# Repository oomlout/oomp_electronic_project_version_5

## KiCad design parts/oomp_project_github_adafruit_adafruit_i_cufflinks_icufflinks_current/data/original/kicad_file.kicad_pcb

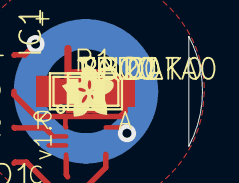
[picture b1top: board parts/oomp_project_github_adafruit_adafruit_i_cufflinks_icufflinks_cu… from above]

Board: 2 copper layers, 12 parts (0 on the bottom side), 7 nets.

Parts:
GND0: TPTP10R; TP10R
IC1: ATTINY10-MAHR; UDFN-8
LED1: SMLK34
PB2: TPTP10R; TP10R
R1: R0805
RST0: TPTP10R; TP10R
TPICLK0: TPTP10R; TP10R
TPIDATA0: TPTP10R; TP10R
U$1: ADAFRUIT200MIL
U$2, U$3: FIDUCIAL; TP_SIGNAL_NAME!
VCC0: TPTP10R; TP10R

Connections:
B0: IC1.5, LED1.K, TPIDATA0.TP
B1: IC1.1, TPICLK0.TP
B2: IC1.8, PB2.TP
GND: GND0.TP, IC1.4
unnamed: LED1.A, R1.1
RST: IC1.6, RST0.TP
VCC: IC1.7, R1.2, VCC0.TP

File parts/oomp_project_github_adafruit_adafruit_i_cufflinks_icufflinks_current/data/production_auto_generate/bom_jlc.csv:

Comment,Designator,Footprint,LCSC Part #
,U$1,cuff-import-fps:ADAFRUIT200MIL,
,R1,cuff-import-fps:R0805,
,LED1,cuff-import-fps:SMLK34,
ATTINY10-MAHR,IC1,cuff-import-fps:UDFN-8,
FIDUCIAL,"U$2,U$3",cuff-import-fps:TP_SIGNAL_NAME!,
TPTP10R,"GND0,PB2,RST0,TPICLK0,TPIDATA0,VCC0",cuff-import-fps:TP10R,

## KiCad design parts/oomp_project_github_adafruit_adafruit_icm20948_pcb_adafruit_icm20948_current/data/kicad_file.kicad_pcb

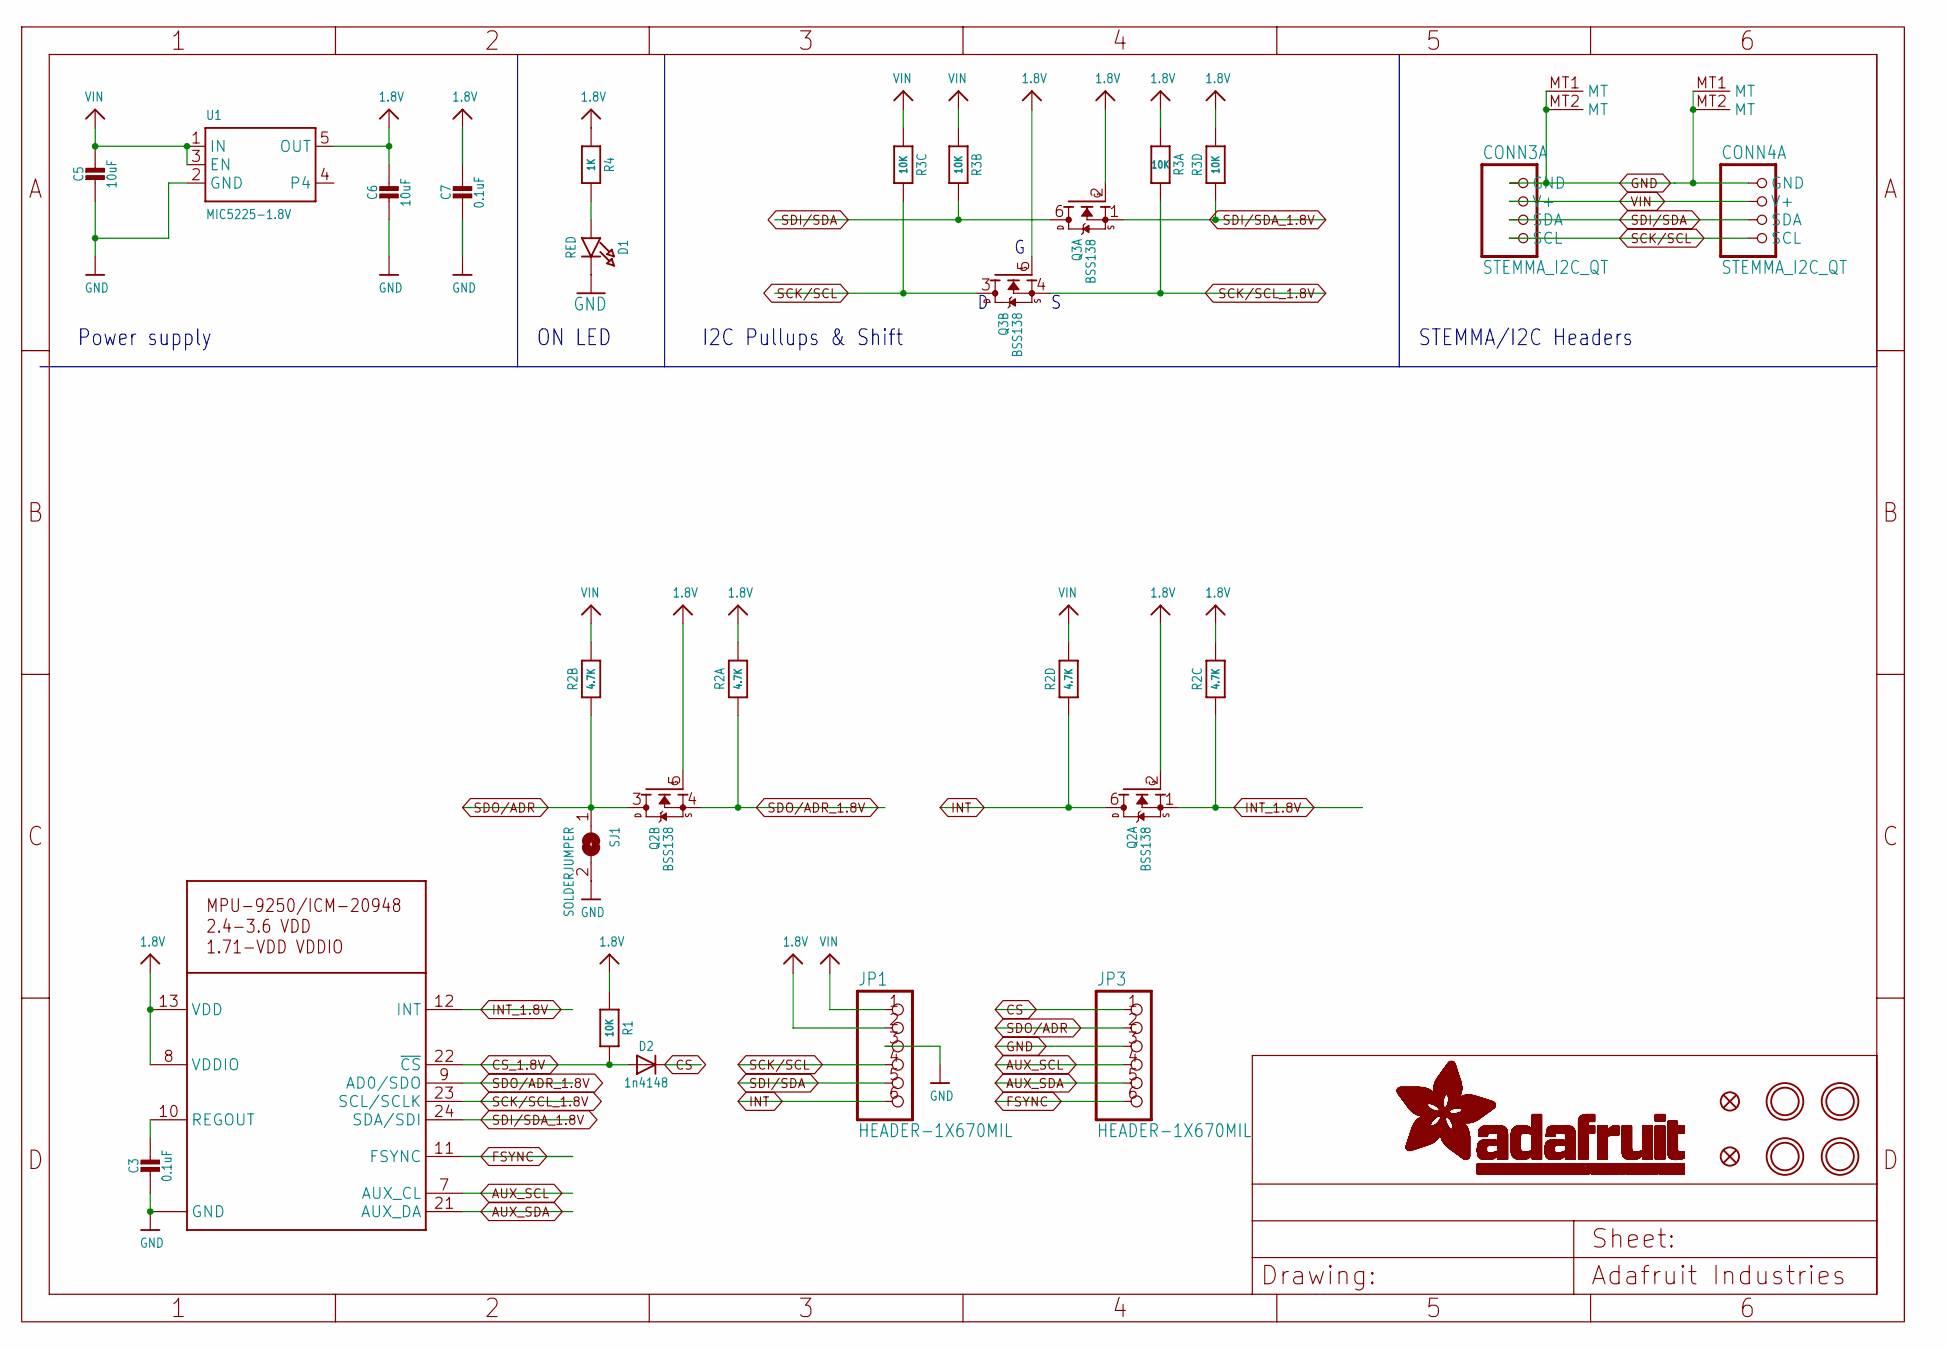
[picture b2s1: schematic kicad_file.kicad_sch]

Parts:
C3, C7: 0.1uF; 0603-NO
C5, C6: 10uF; 0805-NO
CONN3, CONN4: STEMMA_I2C_QT; JST_SH4
D1: RED; CHIPLED_0603_NOOUTLINE
D2: 1n4148; SOD-323_MINI
FID2, FID4: FIDUCIAL_1MM
JP1, JP3: HEADER-1X670MIL; 1X06_ROUND_70
Q2, Q3: BSS138; SOT363
R1: 10K; 0603-NO
R2: 4.7K; RESPACK_4X0603
R3: 10K; RESPACK_4X0603
R4: 1K; 0603-NO
SJ1: SOLDERJUMPER; SOLDERJUMPER_ARROW_NOPASTE
U1: MIC5225-1.8V; SOT23-5
U$21: MPU-9250_ICM20948; QFN24_3MM_NOEP
U$38, U$39, U$41, U$42: MOUNTINGHOLE2.5; MOUNTINGHOLE_2.5_PLATED

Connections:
1.8V: C6.1, C7.1, JP1.2, Q2.2 (G), Q2.5 (G), Q3.2 (G), Q3.5 (G), R1.1, R2.6 (2), R2.8 (2), R3.4 (1), R3.8 (2), R4.1, U1.5 (OUT), U$21.8 (VDDIO), U$21.13 (VDD)
AUX_SCL: JP3.4, U$21.7 (AUX_CL)
AUX_SDA: JP3.5, U$21.21 (AUX_DA)
CS: D2.C, JP3.1
CS_1.8V: D2.A, R1.2, U$21.22 (~CS)
FSYNC: JP3.6, U$21.11 (FSYNC)
GND: C3.2, C5.2, C6.2, C7.2, CONN3.1 (GND), CONN3.MT1 (MT), CONN3.MT2 (MT), CONN4.1 (GND), CONN4.MT1 (MT), CONN4.MT2 (MT), D1.C, JP1.3, JP3.3, SJ1.2, U1.2 (GND), U$21.18 (GND), U$21.20 (GND)
INT: JP1.6, Q2.6 (D), R2.4 (1)
INT_1.8V: Q2.1 (S), R2.3 (1), U$21.12 (INT)
unnamed: D1.A, R4.2
REGOUT: C3.1, U$21.10 (REGOUT)
SCK/SCL: CONN3.4 (SCL), CONN4.4 (SCL), JP1.4, Q3.3 (D), R3.6 (2)
SCK/SCL_1.8V: Q3.4 (S), R3.1, U$21.23 (SCL/SCLK)
SDI/SDA: CONN3.3 (SDA), CONN4.3 (SDA), JP1.5, Q3.6 (D), R3.7 (2)
SDI/SDA_1.8V: Q3.1 (S), R3.5 (2), U$21.24 (SDA/SDI)
SDO/ADR: JP3.2, Q2.3 (D), R2.2 (1), SJ1.1
SDO/ADR_1.8V: Q2.4 (S), R2.1, U$21.9 (AD0/SDO)
VIN: C5.1, CONN3.2 (V+), CONN4.2 (V+), JP1.1, R2.5 (2), R2.7 (2), R3.2 (1), R3.3 (1), U1.1 (IN), U1.3 (EN)

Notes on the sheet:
STEMMA/I2C Headers
Power supply
I2C Pullups & Shift
ON LED

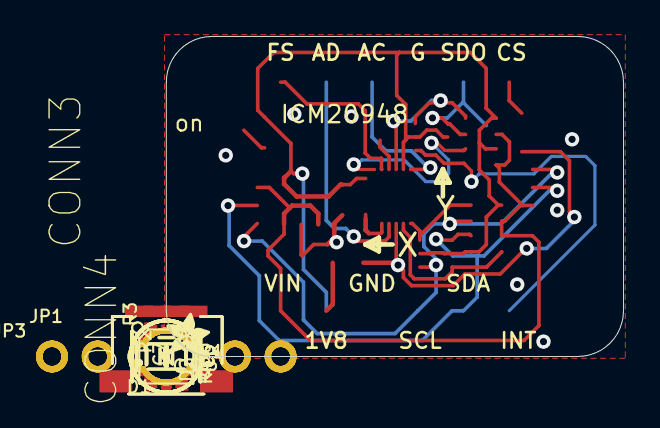
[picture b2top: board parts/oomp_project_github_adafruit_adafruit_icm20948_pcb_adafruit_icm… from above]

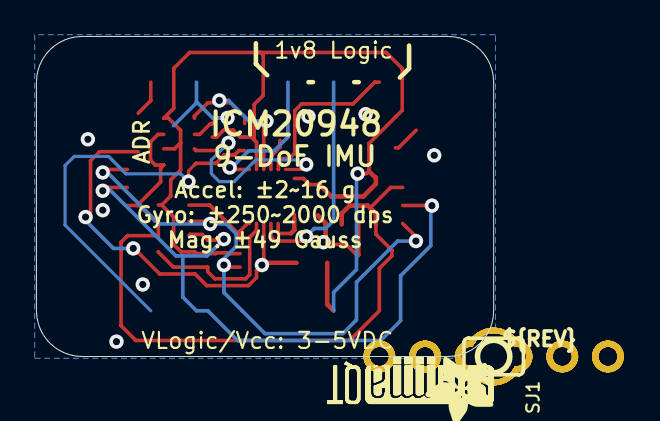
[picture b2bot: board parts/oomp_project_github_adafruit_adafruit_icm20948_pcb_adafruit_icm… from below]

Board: 2 copper layers, 25.4 x 17.8 mm, 30 parts (5 on the bottom side), 18 nets.

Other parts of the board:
U$2: ADAFRUIT_2.5MM
U$12: ADAFRUIT_3.5MM
U$45: PCBFEAT-REV-040
U$46, U$47: STEMMAQT

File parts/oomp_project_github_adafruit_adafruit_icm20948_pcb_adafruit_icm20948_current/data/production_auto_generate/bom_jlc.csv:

Comment,Designator,Footprint,LCSC Part #
,"JP1,JP3",Adafruit ICM20948-import-fps:1X06_ROUND_70,C37208
,U$2,Adafruit ICM20948-import-fps:ADAFRUIT_2.5MM,
,U$12,Adafruit ICM20948-import-fps:ADAFRUIT_3.5MM,
,U$45,Adafruit ICM20948-import-fps:PCBFEAT-REV-040,
,"U$46,U$47",Adafruit ICM20948-import-fps:STEMMAQT,
0.1uF,"C3,C7",Adafruit ICM20948-import-fps:0603-NO,C14663
10K,R1,Adafruit ICM20948-import-fps:0603-NO,C98220
10K,R3,Adafruit ICM20948-import-fps:RESPACK_4X0603,C98220
10uF,"C5,C6",Adafruit ICM20948-import-fps:0805-NO,
1K,R4,Adafruit ICM20948-import-fps:0603-NO,C2907002
1n4148,D2,Adafruit ICM20948-import-fps:SOD-323_MINI,
4.7K,R2,Adafruit ICM20948-import-fps:RESPACK_4X0603,C23162
BSS138,"Q2,Q3",Adafruit ICM20948-import-fps:SOT363,
MIC5225-1.8V,U1,Adafruit ICM20948-import-fps:SOT23-5,
MPU-9250_ICM20948,U$21,Adafruit ICM20948-import-fps:QFN24_3MM_NOEP,
RED,D1,Adafruit ICM20948-import-fps:CHIPLED_0603_NOOUTLINE,
STEMMA_I2C_QT,"CONN3,CONN4",Adafruit ICM20948-import-fps:JST_SH4,C160404

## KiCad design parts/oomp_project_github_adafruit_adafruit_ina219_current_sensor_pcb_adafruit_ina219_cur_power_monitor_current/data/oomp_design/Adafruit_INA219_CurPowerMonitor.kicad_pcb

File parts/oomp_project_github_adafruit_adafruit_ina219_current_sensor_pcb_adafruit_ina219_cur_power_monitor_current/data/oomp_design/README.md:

# OOMP KiCad design copy

Open `Adafruit_INA219_CurPowerMonitor.kicad_pro` (or the `.kicad_pcb` / `.kicad_sch`) in KiCad. Local OOMP libraries are under `libraries/`. Original inputs are preserved in [../original/](../original/).

Only verified unchanged installed KiCad defaults were renamed. Modified, custom, unmatched and unavailable items remain unchanged. Soldering variants are never swapped during conversion. Existing pad coordinates, nets and UUIDs are preserved.

See [conversion_report.yaml](conversion_report.yaml) for every conversion and skip. Copy this directory before editing; regeneration refuses to overwrite edited design files.

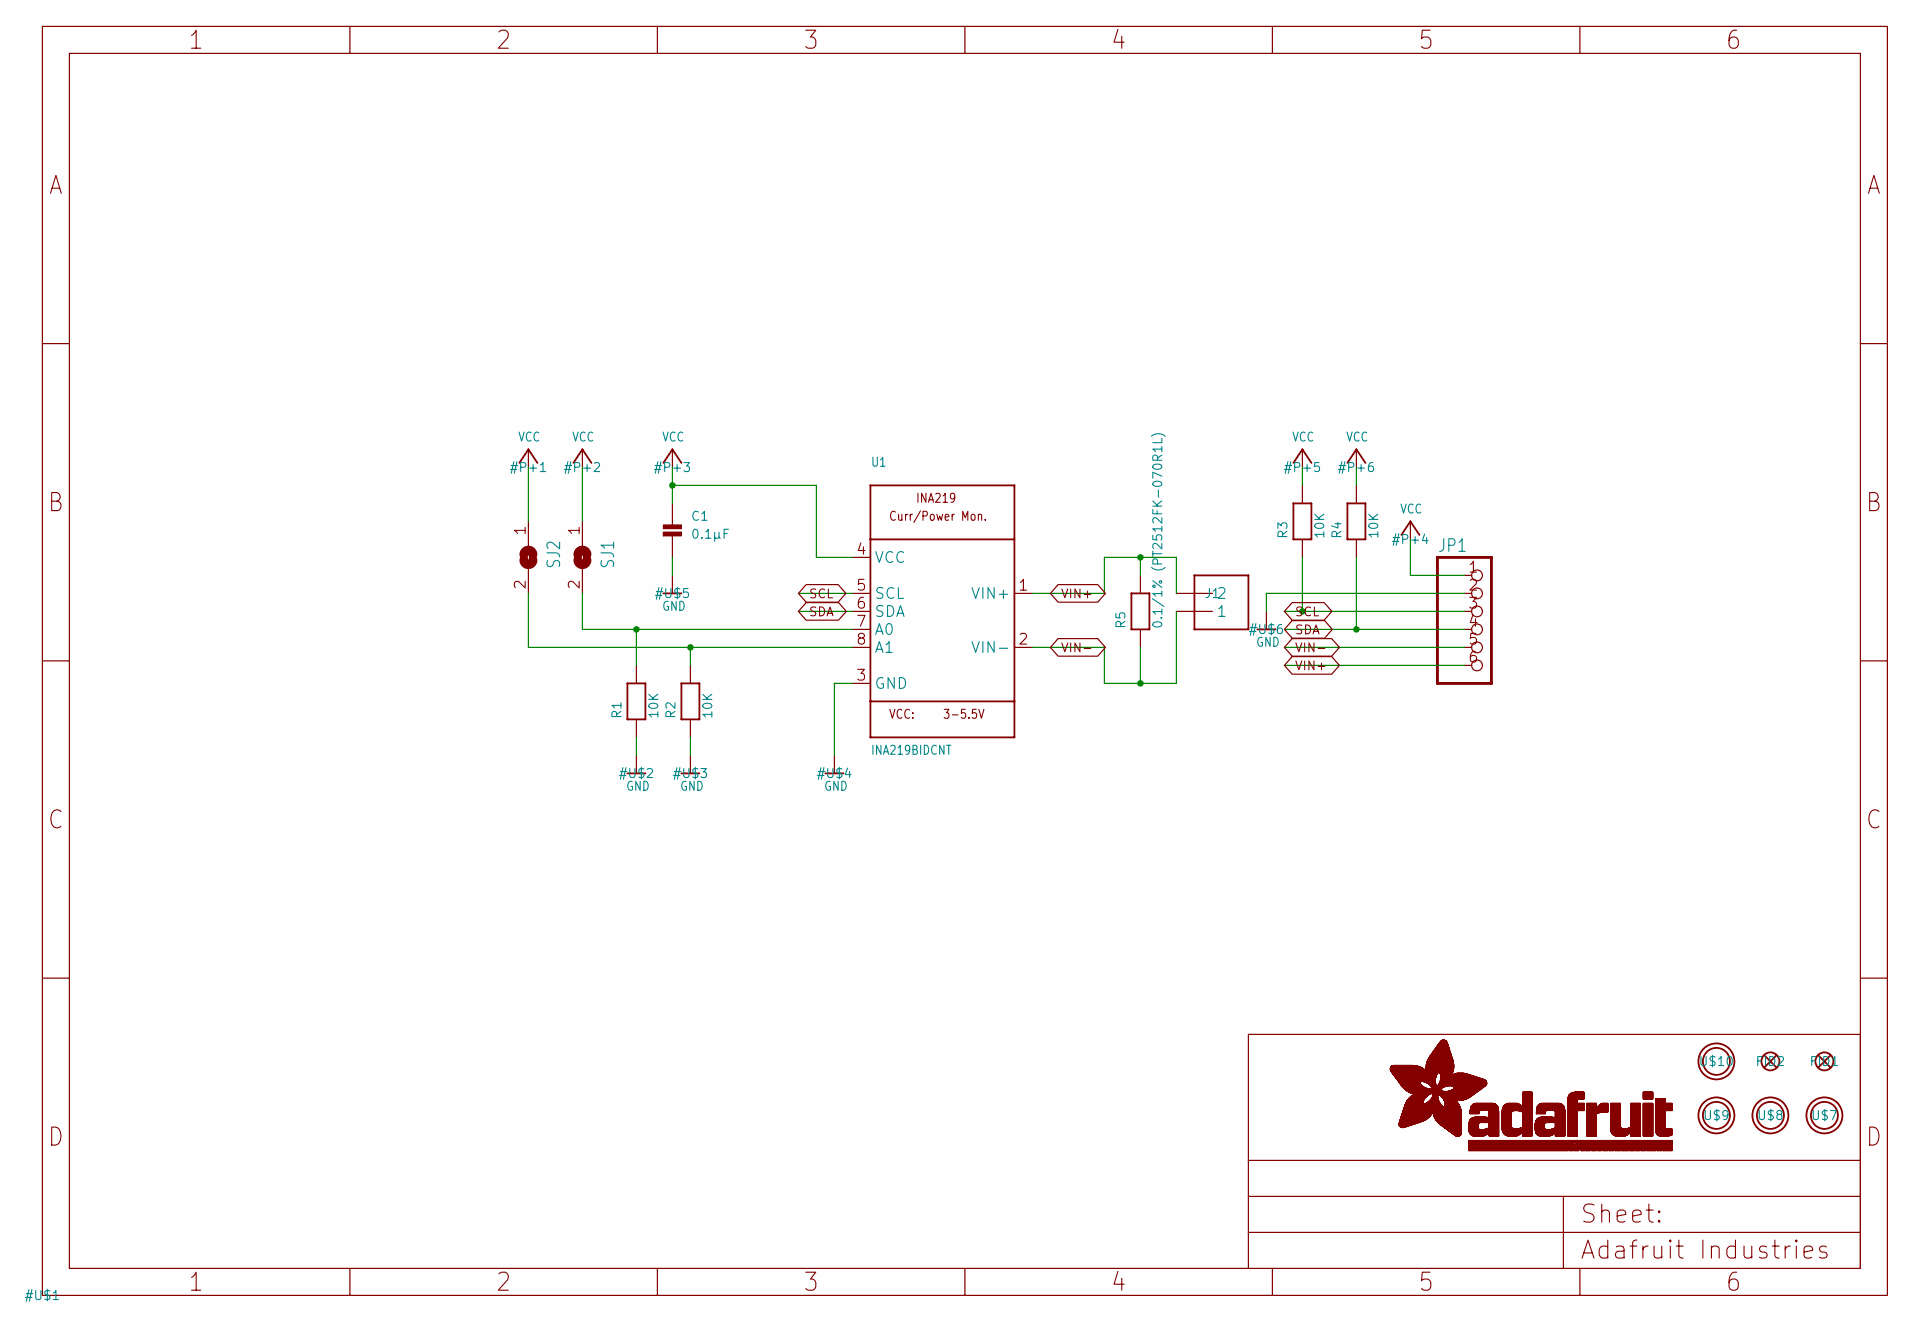
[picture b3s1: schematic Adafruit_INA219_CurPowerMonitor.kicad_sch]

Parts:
C1: 0.1µF; 0805
FID1, FID2: FIDUCIAL""; FIDUCIAL_1MM
J1: TERMBLOCK_1X2-3.5MM; 1X2-3.5MM
JP1: HEADER-1X670MIL; 1X06_ROUND_70
R1, R2, R3, R4: 10K; 0805
R5: 0.1/1% (PT2512FK-070R1L); 2512
SJ1, SJ2: SOLDERJUMPERREFLOW_NOPASTE; SOLDERJUMPER_REFLOW_NOPASTE
U1: INA219BIDCNT; SOT23-8
U$7, U$8, U$9, U$10: MOUNTINGHOLE2.5; MOUNTINGHOLE_2.5_PLATED

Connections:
GND: C1.2, JP1.2, R1.1, R2.1, U1.3 (GND)
unnamed: R2.2, SJ2.2, U1.8 (A1)
unnamed: R1.2, SJ1.2, U1.7 (A0)
SCL: JP1.3, R3.1, U1.5 (SCL)
SDA: JP1.4, R4.1, U1.6 (SDA)
VCC: C1.1, JP1.1, R3.2, R4.2, SJ1.1, SJ2.1, U1.4 (VCC)
VIN+: J1.2, JP1.6, R5.2, U1.1 (VIN+)
VIN-: J1.1, JP1.5, R5.1, U1.2 (VIN-)

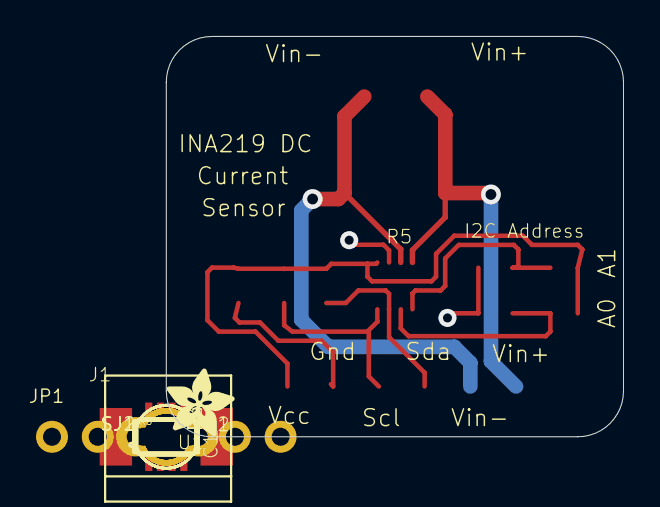
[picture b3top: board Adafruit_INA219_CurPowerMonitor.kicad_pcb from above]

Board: 2 copper layers, 25.4 x 22.2 mm, 18 parts (0 on the bottom side), 8 nets.

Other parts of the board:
U$11: ADAFRUIT_3.5MM

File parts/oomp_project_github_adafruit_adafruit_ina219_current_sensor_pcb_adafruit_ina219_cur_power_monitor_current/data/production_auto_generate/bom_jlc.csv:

Comment,Designator,Footprint,LCSC Part #
,JP1,Adafruit_INA219_CurPowerMonitor-import-fps:1X06_ROUND_70,C37208
,U$11,Adafruit_INA219_CurPowerMonitor-import-fps:ADAFRUIT_3.5MM,
0.1/1% (PT2512FK-070R1L),R5,Adafruit_INA219_CurPowerMonitor-import-fps:2512,
0.1µF,C1,Adafruit_INA219_CurPowerMonitor-import-fps:0805,
10K,"R1,R2,R3,R4",Adafruit_INA219_CurPowerMonitor-import-fps:0805,C17414
INA219BIDCNT,U1,Adafruit_INA219_CurPowerMonitor-import-fps:SOT23-8,
TERMBLOCK_1X2-3.5MM,J1,Adafruit_INA219_CurPowerMonitor-import-fps:1X2-3.5MM,C492401

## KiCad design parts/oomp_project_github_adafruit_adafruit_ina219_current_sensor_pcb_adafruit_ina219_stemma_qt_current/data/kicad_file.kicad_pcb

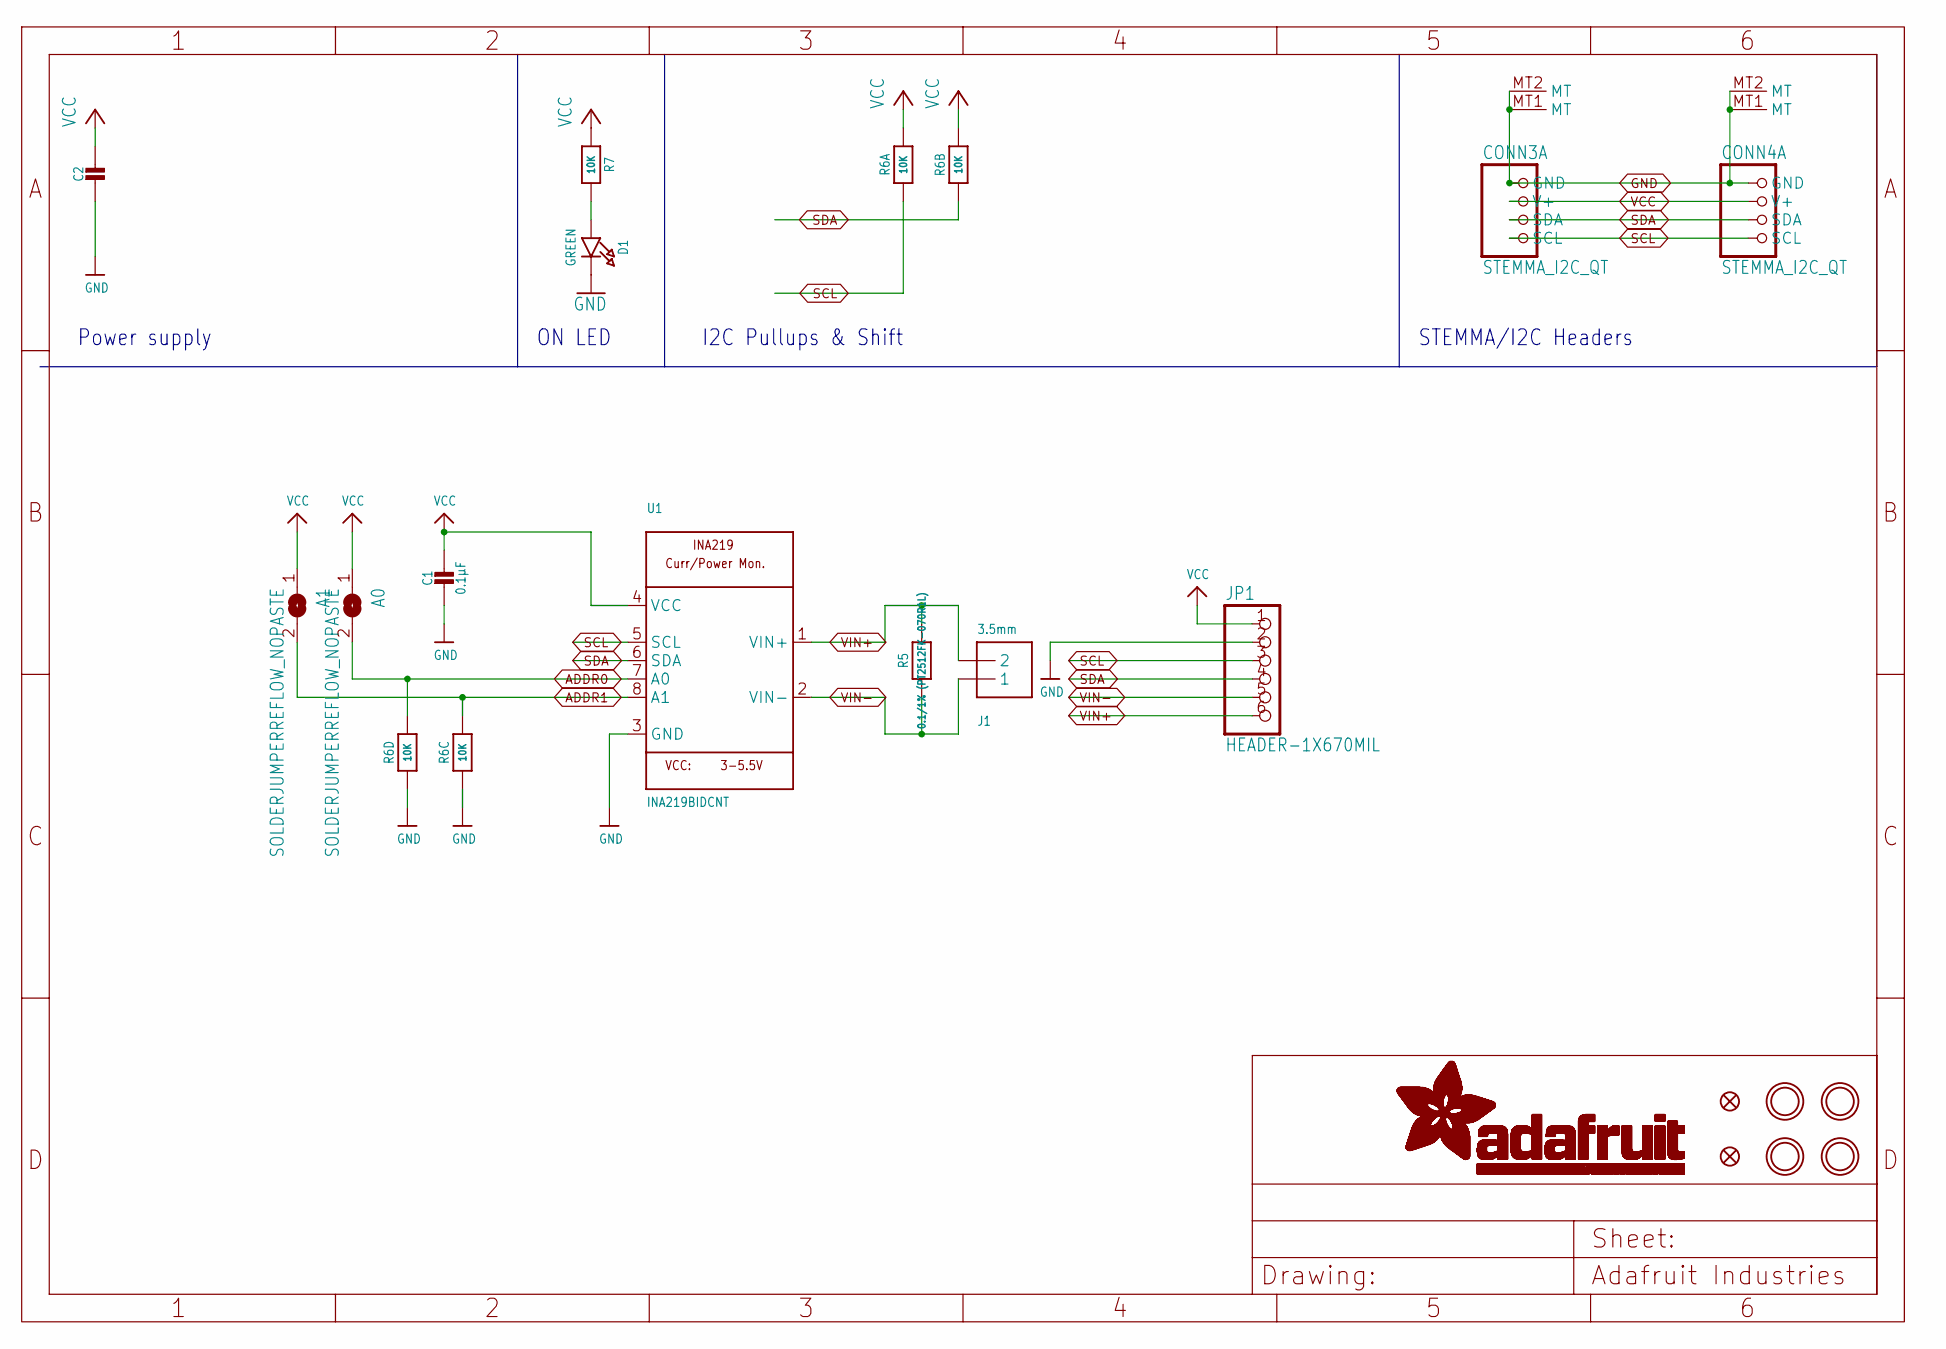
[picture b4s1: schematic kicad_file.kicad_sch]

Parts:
A0, A1: SOLDERJUMPERREFLOW_NOPASTE; SOLDERJUMPER_REFLOW_NOPASTE
C1: 0.1µF; 0603-NO
C2: 10uF; 0805-NO
CONN3, CONN4: STEMMA_I2C_QT; JST_SH4
D1: GREEN; CHIPLED_0603_NOOUTLINE
FID3, FID4: FIDUCIAL_1MM
J1: 3.5mm; TERMBLOCK_1X2-3.5MM
JP1: HEADER-1X670MIL; 1X06_ROUND_70
R5: 0.1/1% (PT2512FK-070R1L); 2512
R6: 10K; RESPACK_4X0603
R7: 10K; 0603-NO
U1: INA219BIDCNT; SOT23-8
U$20, U$21, U$25, U$27: MOUNTINGHOLE2.5; MOUNTINGHOLE_2.5_PLATED

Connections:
ADDR0: A0.2, R6.5 (2), U1.7 (A0)
ADDR1: A1.2, R6.6 (2), U1.8 (A1)
GND: C1.2, C2.2, CONN3.1 (GND), CONN3.MT1 (MT), CONN3.MT2 (MT), CONN4.1 (GND), CONN4.MT1 (MT), CONN4.MT2 (MT), D1.C, JP1.2, R6.3 (1), R6.4 (1), U1.3 (GND)
unnamed: D1.A, R7.2
SCL: CONN3.4 (SCL), CONN4.4 (SCL), JP1.3, R6.1, U1.5 (SCL)
SDA: CONN3.3 (SDA), CONN4.3 (SDA), JP1.4, R6.2 (1), U1.6 (SDA)
VCC: A0.1, A1.1, C1.1, C2.1, CONN3.2 (V+), CONN4.2 (V+), JP1.1, R6.7 (2), R6.8 (2), R7.1, U1.4 (VCC)
VIN+: J1.2, JP1.6, R5.2, U1.1 (VIN+)
VIN-: J1.1, JP1.5, R5.1, U1.2 (VIN-)

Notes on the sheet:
ON LED
I2C Pullups & Shift
Power supply
STEMMA/I2C Headers

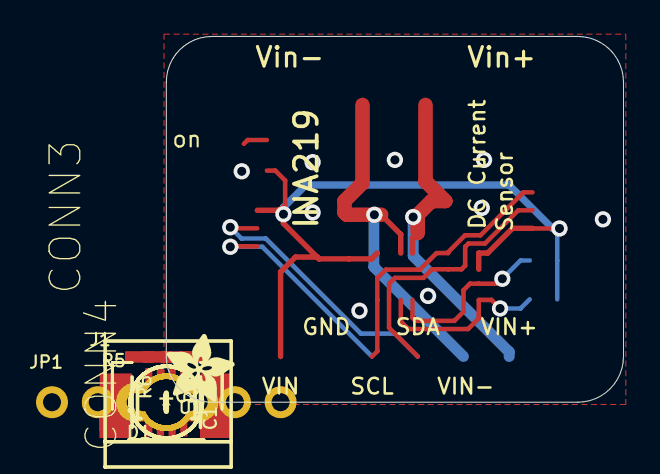
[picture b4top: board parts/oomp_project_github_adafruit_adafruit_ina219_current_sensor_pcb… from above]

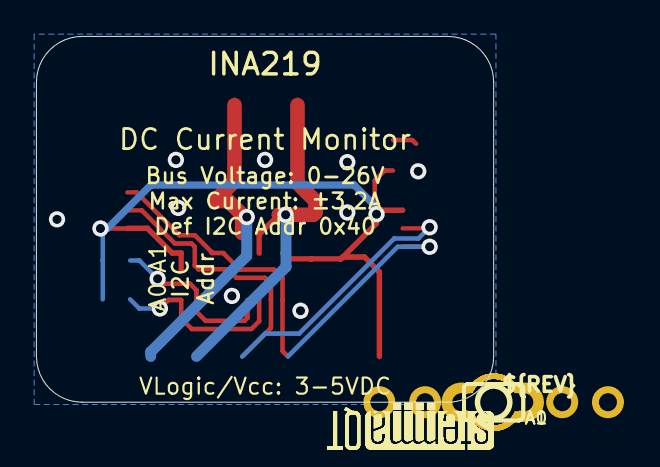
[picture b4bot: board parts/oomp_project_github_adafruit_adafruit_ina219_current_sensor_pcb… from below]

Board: 2 copper layers, 25.4 x 20.3 mm, 23 parts (5 on the bottom side), 9 nets.

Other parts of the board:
U$29: ADAFRUIT_3.5MM
U$30: PCBFEAT-REV-040
U$31, U$32: STEMMAQT

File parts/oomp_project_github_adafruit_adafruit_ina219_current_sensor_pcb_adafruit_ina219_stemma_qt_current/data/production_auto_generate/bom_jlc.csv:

Comment,Designator,Footprint,LCSC Part #
,JP1,Adafruit INA219 STEMMA QT-import-fps:1X06_ROUND_70,C37208
,U$29,Adafruit INA219 STEMMA QT-import-fps:ADAFRUIT_3.5MM,
,U$30,Adafruit INA219 STEMMA QT-import-fps:PCBFEAT-REV-040,
,"A0,A1",Adafruit INA219 STEMMA QT-import-fps:SOLDERJUMPER_REFLOW_NOPASTE,
,"U$31,U$32",Adafruit INA219 STEMMA QT-import-fps:STEMMAQT,
0.1/1% (PT2512FK-070R1L),R5,Adafruit INA219 STEMMA QT-import-fps:2512,
0.1µF,C1,Adafruit INA219 STEMMA QT-import-fps:0603-NO,C14663
10K,R7,Adafruit INA219 STEMMA QT-import-fps:0603-NO,C98220
10K,R6,Adafruit INA219 STEMMA QT-import-fps:RESPACK_4X0603,C98220
10uF,C2,Adafruit INA219 STEMMA QT-import-fps:0805-NO,
3.5mm,J1,Adafruit INA219 STEMMA QT-import-fps:TERMBLOCK_1X2-3.5MM,
GREEN,D1,Adafruit INA219 STEMMA QT-import-fps:CHIPLED_0603_NOOUTLINE,
INA219BIDCNT,U1,Adafruit INA219 STEMMA QT-import-fps:SOT23-8,
STEMMA_I2C_QT,"CONN3,CONN4",Adafruit INA219 STEMMA QT-import-fps:JST_SH4,C160404

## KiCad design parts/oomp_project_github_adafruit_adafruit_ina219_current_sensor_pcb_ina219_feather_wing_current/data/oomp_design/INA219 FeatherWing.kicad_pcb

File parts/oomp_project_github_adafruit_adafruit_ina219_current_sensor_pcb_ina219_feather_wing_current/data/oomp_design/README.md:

# OOMP KiCad design copy

Open `INA219 FeatherWing.kicad_pro` (or the `.kicad_pcb` / `.kicad_sch`) in KiCad. Local OOMP libraries are under `libraries/`. Original inputs are preserved in [../original/](../original/).

Only verified unchanged installed KiCad defaults were renamed. Modified, custom, unmatched and unavailable items remain unchanged. Soldering variants are never swapped during conversion. Existing pad coordinates, nets and UUIDs are preserved.

See [conversion_report.yaml](conversion_report.yaml) for every conversion and skip. Copy this directory before editing; regeneration refuses to overwrite edited design files.

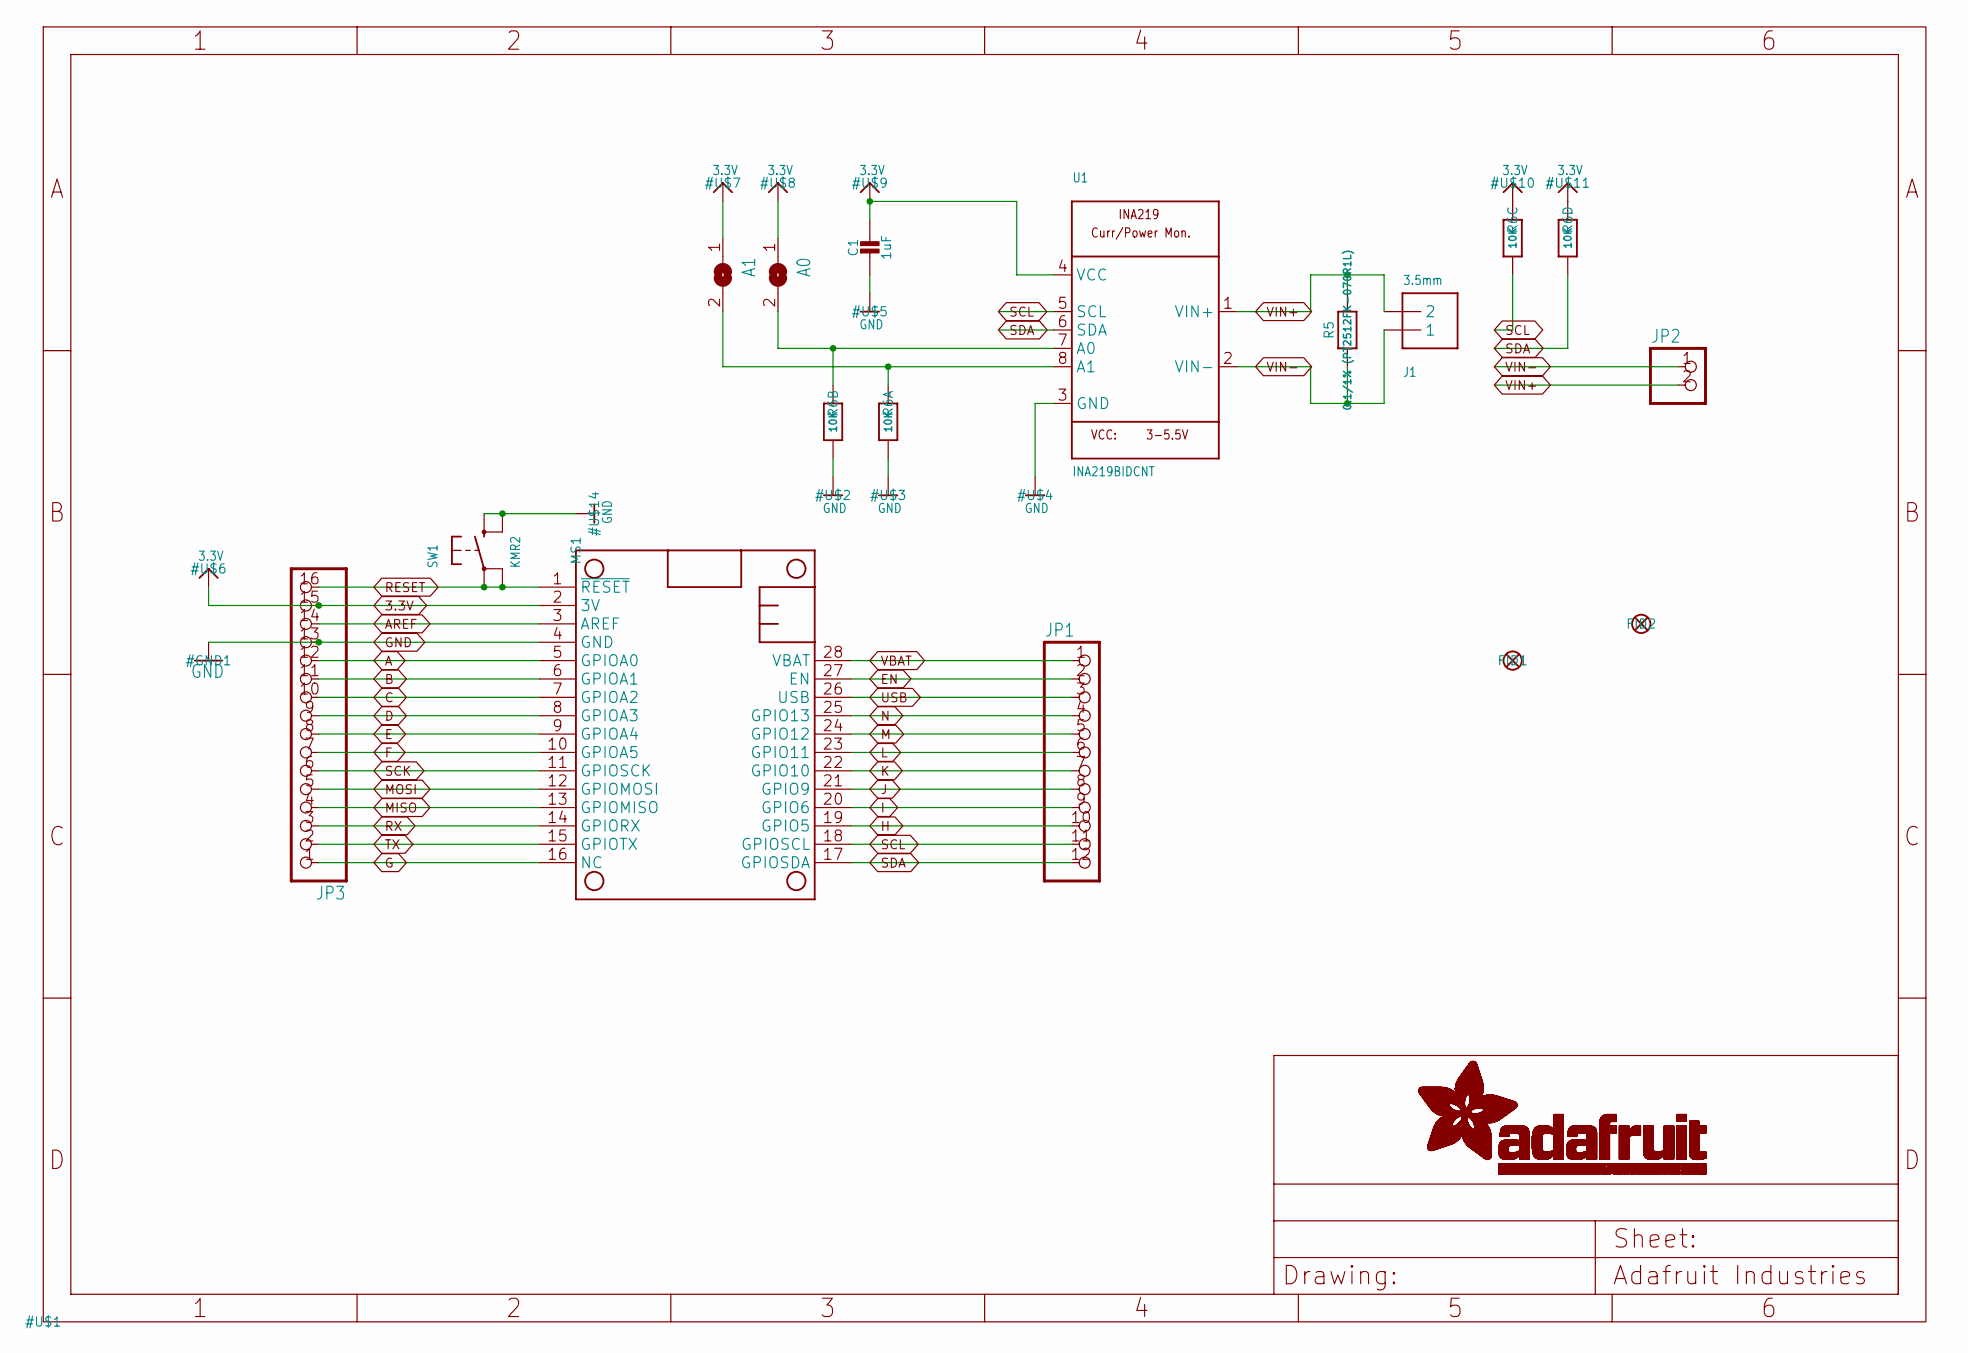
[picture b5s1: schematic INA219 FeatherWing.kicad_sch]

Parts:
A0, A1: SOLDERJUMPERREFLOW_NOPASTE; SOLDERJUMPER_REFLOW_NOPASTE
C1: 1uF; 0805-NO@1
FID1, FID2: FIDUCIAL_1MM
J1: 3.5mm; TERMBLOCK_1X2-3.5MM
JP1: HEADER-1X1276MIL; 1X12_ROUND_76MIL
JP2: HEADER-1X2ROUND; 1X02_ROUND
JP3: HEADER-1X16_76MIL; 1X16_ROUND_76MIL
MS1: FEATHERWING
R5: 0.1/1% (PT2512FK-070R1L); 2512
R6: 10K; RESPACK_4X0603
SW1: KMR2; BTN_KMR2_4.6X2.8
U1: INA219BIDCNT; SOT23-8

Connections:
3.3V: A0.1, A1.1, C1.1, JP3.15, MS1.2 (3V), R6.5 (2), R6.6 (2), U1.4 (VCC)
A: JP3.12, MS1.5 (GPIOA0)
AREF: JP3.14, MS1.3 (AREF)
B: JP3.11, MS1.6 (GPIOA1)
C: JP3.10, MS1.7 (GPIOA2)
D: JP3.9, MS1.8 (GPIOA3)
E: JP3.8, MS1.9 (GPIOA4)
EN: JP1.2, MS1.27 (EN)
F: JP3.7, MS1.10 (GPIOA5)
G: JP3.1, MS1.16 (NC)
GND: C1.2, JP3.13, MS1.4 (GND), R6.7 (2), R6.8 (2), SW1.B (S), SW1.B' (S1), U1.3 (GND)
H: JP1.10, MS1.19 (GPIO5)
I: JP1.9, MS1.20 (GPIO6)
J: JP1.8, MS1.21 (GPIO9)
K: JP1.7, MS1.22 (GPIO10)
L: JP1.6, MS1.23 (GPIO11)
M: JP1.5, MS1.24 (GPIO12)
MISO: JP3.4, MS1.13 (GPIOMISO)
MOSI: JP3.5, MS1.12 (GPIOMOSI)
N: JP1.4, MS1.25 (GPIO13)
unnamed: A1.2, R6.1, U1.8 (A1)
unnamed: A0.2, R6.2 (1), U1.7 (A0)
RESET: JP3.16, MS1.1 (~RESET), SW1.A, SW1.A' (P1)
RX: JP3.3, MS1.14 (GPIORX)
SCK: JP3.6, MS1.11 (GPIOSCK)
SCL: JP1.11, MS1.18 (GPIOSCL), R6.3 (1), U1.5 (SCL)
SDA: JP1.12, MS1.17 (GPIOSDA), R6.4 (1), U1.6 (SDA)
TX: JP3.2, MS1.15 (GPIOTX)
USB: JP1.3, MS1.26 (USB)
VBAT: JP1.1, MS1.28 (VBAT)
VIN+: J1.2, JP2.2, R5.2, U1.1 (VIN+)
VIN-: J1.1, JP2.1, R5.1, U1.2 (VIN-)

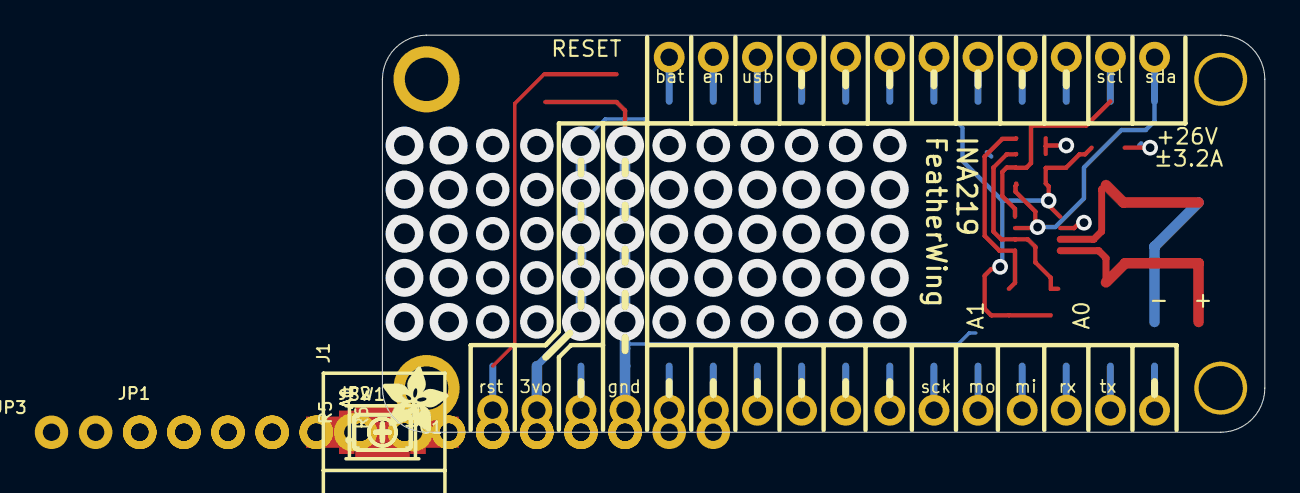
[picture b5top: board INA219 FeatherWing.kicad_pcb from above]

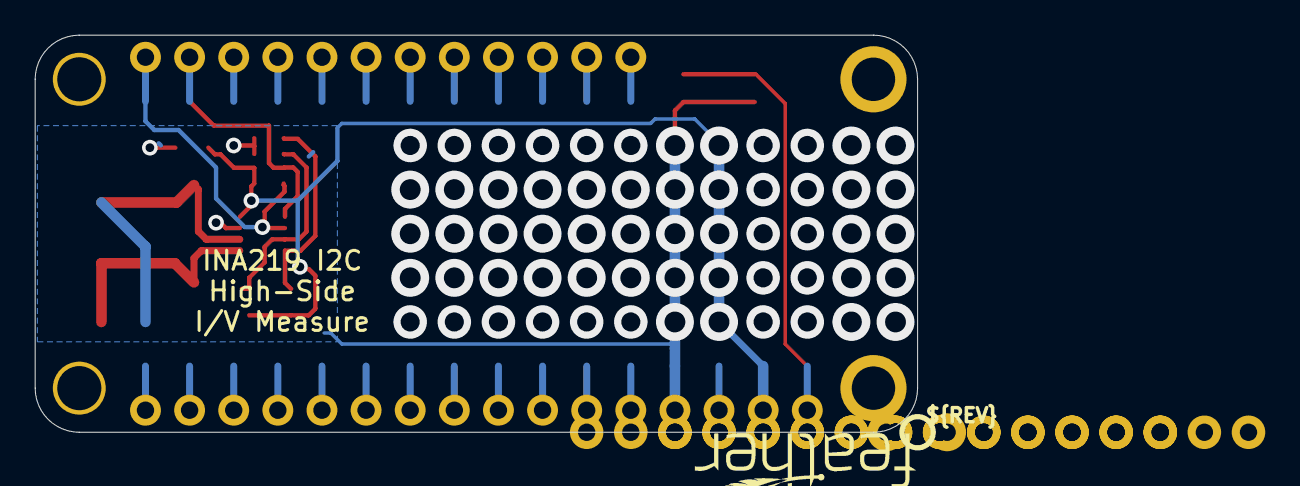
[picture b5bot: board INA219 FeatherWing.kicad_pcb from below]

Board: 2 copper layers, 50.8 x 22.9 mm, 19 parts (2 on the bottom side), 32 nets.

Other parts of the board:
U$12: SYMBOL_PLUS
U$13: SYMBOL_MINUS
U$15: FEATHERLOGO_SMALL
U$16: ADAFRUIT_3.5MM
U$17: PCBFEAT-REV-040

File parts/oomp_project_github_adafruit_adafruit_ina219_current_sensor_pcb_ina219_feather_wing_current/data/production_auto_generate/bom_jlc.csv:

Comment,Designator,Footprint,LCSC Part #
,JP2,INA219 FeatherWing-import-fps:1X02_ROUND,C492401
,JP1,INA219 FeatherWing-import-fps:1X12_ROUND_76MIL,C7501588
,JP3,INA219 FeatherWing-import-fps:1X16_ROUND_76MIL,C7501270
,U$16,INA219 FeatherWing-import-fps:ADAFRUIT_3.5MM,
,U$15,INA219 FeatherWing-import-fps:FEATHERLOGO_SMALL,
,U$17,INA219 FeatherWing-import-fps:PCBFEAT-REV-040,
,"A0,A1",INA219 FeatherWing-import-fps:SOLDERJUMPER_REFLOW_NOPASTE,
,U$13,INA219 FeatherWing-import-fps:SYMBOL_MINUS,
,U$12,INA219 FeatherWing-import-fps:SYMBOL_PLUS,
0.1/1% (PT2512FK-070R1L),R5,INA219 FeatherWing-import-fps:2512,
10K,R6,INA219 FeatherWing-import-fps:RESPACK_4X0603,C98220
1uF,C1,INA219 FeatherWing-import-fps:0805-NO@1,
3.5mm,J1,INA219 FeatherWing-import-fps:TERMBLOCK_1X2-3.5MM,
FEATHERWING,MS1,INA219 FeatherWing-import-fps:FEATHERWING,
INA219BIDCNT,U1,INA219 FeatherWing-import-fps:SOT23-8,
KMR2,SW1,INA219 FeatherWing-import-fps:BTN_KMR2_4.6X2.8,
